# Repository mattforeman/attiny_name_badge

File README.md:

# attiny_name_badge
simple attiny driven name badge with leds

board should be in working state minus software (incoming).

generate text/images using Svg2Shenzhen (https://github.com/badgeek/svg2shenzhen) plugin and import into KICAD.

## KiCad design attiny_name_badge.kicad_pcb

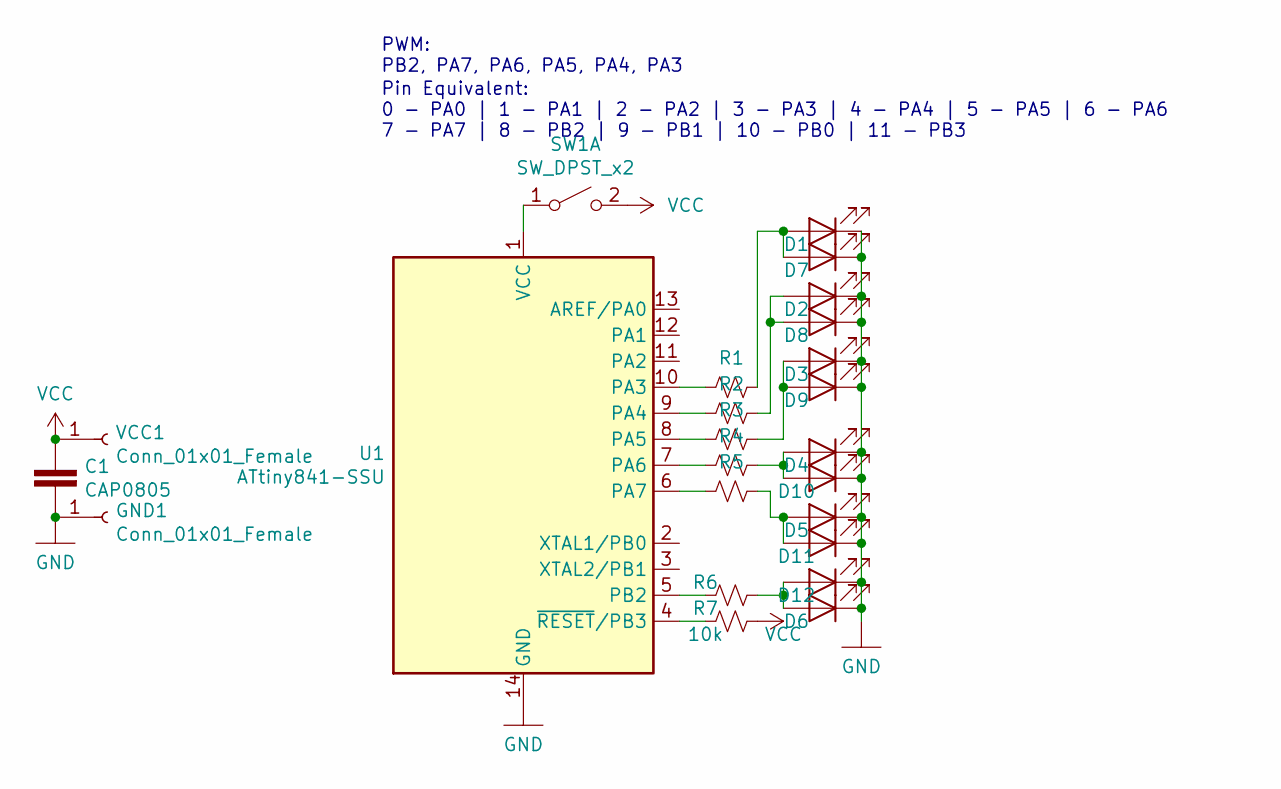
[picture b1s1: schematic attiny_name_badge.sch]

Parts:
C1: CAP0805; C_0805_2012Metric_Pad1.15x1.40mm_HandSolder
D1, D2, D3, D4, D5, D6, D7, D8, D9, D10, D11, D12: LED; LED_0805_2012Metric_Pad1.15x1.40mm_HandSolder
GND1: Conn_01x01_Female; Pin_D1.0mm_L10.0mm_LooseFit
R1, R2, R3, R4, R5, R6: R_Small_US; LED_0805_2012Metric_Pad1.15x1.40mm_HandSolder
R7: 10k; LED_0805_2012Metric_Pad1.15x1.40mm_HandSolder
SW1: SW_DPST_x2; SW_PUSH_6mm_H5mm
U1: ATtiny841-SSU; SOIC-14_3.9x8.7mm_P1.27mm
VCC1: Conn_01x01_Female; Pin_D1.0mm_L10.0mm_LooseFit

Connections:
GND: C1.1, D1.1 (K), D2.1 (K), D3.1 (K), D4.1 (K), D5.1 (K), D6.1 (K), D7.1 (K), D8.1 (K), D9.1 (K), D10.1 (K), D11.1 (K), D12.1 (K), GND1.1, U1.14 (GND)
unnamed: D1.2 (A), D7.2 (A), R1.1
unnamed: D2.2 (A), D8.2 (A), R2.1
unnamed: D3.2 (A), D9.2 (A), R3.1
unnamed: D4.2 (A), D10.2 (A), R4.1
unnamed: D5.2 (A), D11.2 (A), R5.1
unnamed: D6.2 (A), D12.2 (A), R6.1
unnamed: R1.2, U1.10 (PA3)
unnamed: R2.2, U1.9 (PA4)
unnamed: R3.2, U1.8 (PA5)
unnamed: R4.2, U1.7 (PA6)
unnamed: R5.2, U1.6 (PA7)
unnamed: R6.2, U1.5 (PB2)
unnamed: R7.2, U1.4 (~RESET~/PB3)
unnamed: SW1.1 (A), U1.1 (VCC)
VCC: C1.2, R7.1, SW1.2 (B), VCC1.1

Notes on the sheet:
PWM: PB2, PA7, PA6, PA5, PA4, PA3
Pin Equivalent: 0 - PA0 | 1 - PA1 | 2 - PA2 | 3 - PA3 | 4 - PA4 | 5 - PA5 | 6 - PA6 7 - PA7 | 8 - PB2 | 9 - PB1 | 10 - PB0 | 11 - PB3

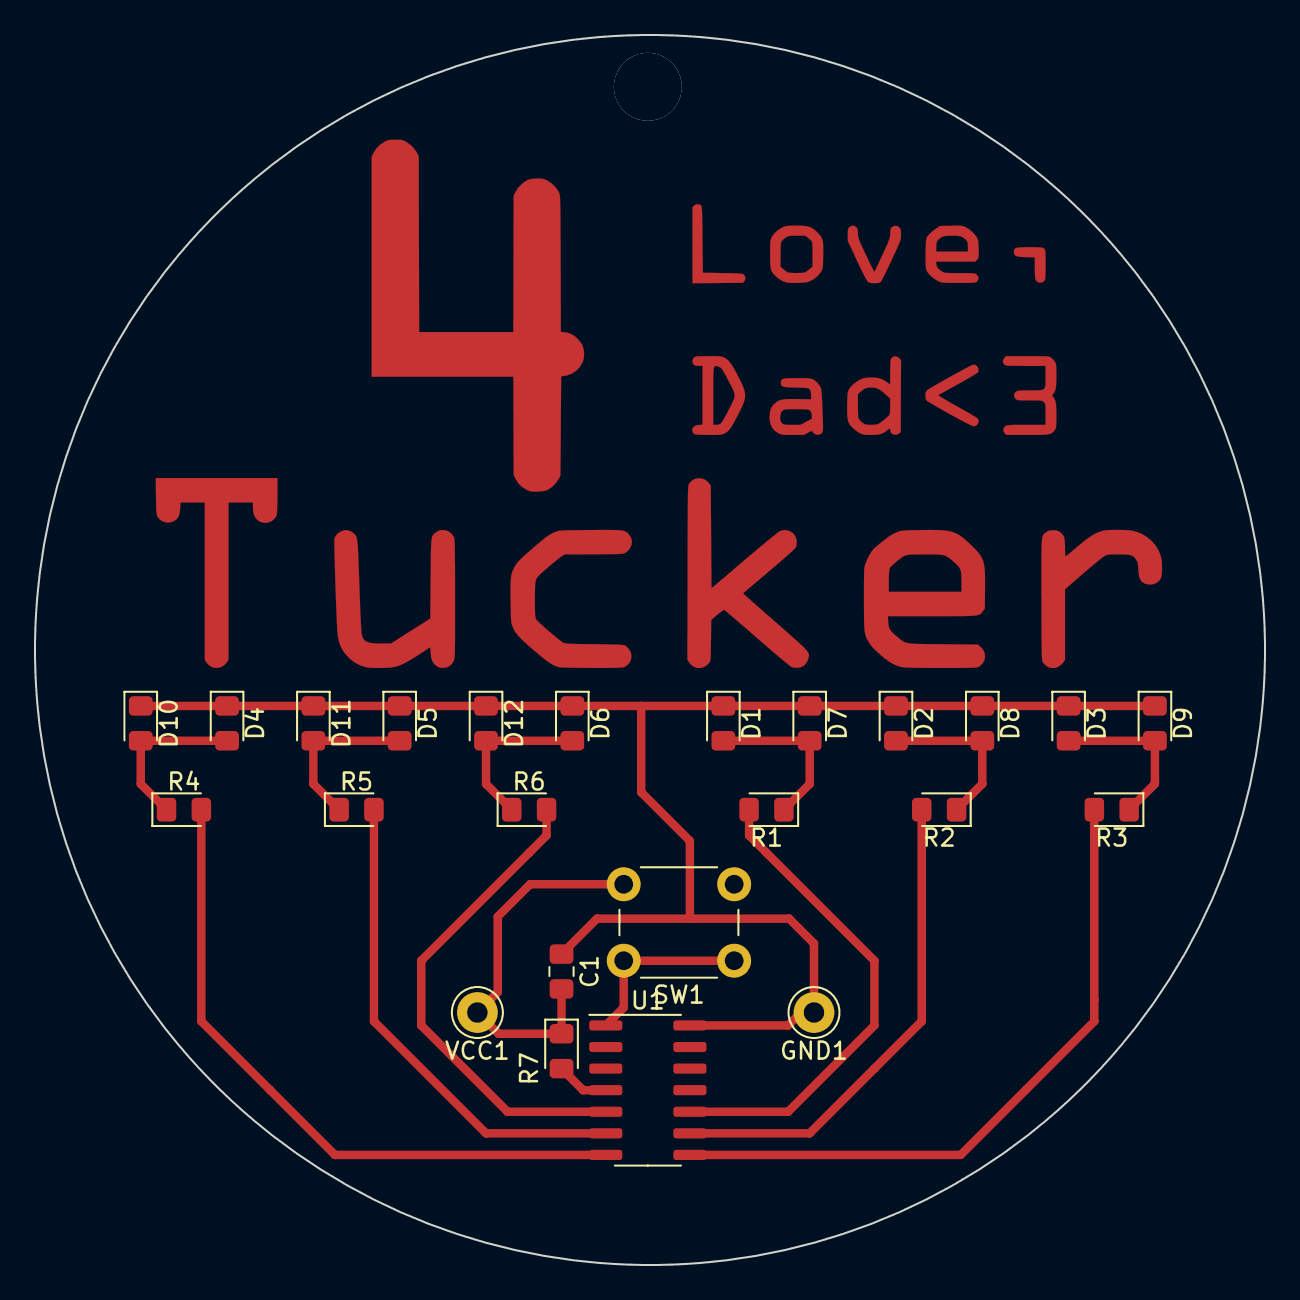
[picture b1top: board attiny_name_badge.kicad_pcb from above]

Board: 2 copper layers, 72.4 x 72.4 mm, 24 parts (0 on the bottom side), 16 nets.

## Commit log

2019-08-28 initial outline
2019-08-29 initial layout
    custom 2032 cell holder
    misc initial placements
2019-08-29 working circuit
    need name/finishing touches
2019-08-30 working board
    cut 'er out!
